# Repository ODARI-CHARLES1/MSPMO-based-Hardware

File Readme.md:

# MSPM0G350x Development Board

A hardware design for an Arduino UNO form-factor development board featuring the Texas Instruments MSPM0G350x Mixed-Signal Microcontroller with built-in CAN-FD interface.

---

## Overview

This project contains the KiCad design files for a custom development board based on the Texas Instruments MSPM0G3507 MCU, featuring CAN-FD connectivity in a familiar Arduino UNO-compatible form factor.

---
## Features

### Microcontroller

- **MCU**: Texas Instruments MSPM0G3507 (or MSPM0G3506)
- **Core**: ARM Cortex-M0+ 32-bit processor
- **Clock Speed**: Up to 80 MHz
- **Flash Memory**: 128 KB (MSPM0G3507) / 64 KB (MSPM0G3506)
- **SRAM**: 32 KB

### Integrated Peripherals

- **CAN-FD Controller**: Built-in CAN-FD with up to 5 Mbps
- **ADC**: 12-bit Analog-to-Digital Converter (up to 20 channels)
- **DAC**: 12-bit Digital-to-Analog Converter (2 channels)
- **Timers**: Multiple 16-bit and 32-bit timers
- **PWM**: High-resolution PWM outputs
- **Communication**: UART, SPI, I2C, DMA

### Board Features

- **Form Factor**: Arduino UNO R3 compatible (2.54mm pitch, 3.3V logic)
- **Power Supply**: 7-12V DC barrel jack or USB-C (5V)
- **USB Interface**: Integrated USB-C for programming and debug
- **CAN Connector**: Standard DB9 or 4-pin header for CAN-FD
- **Power LED**: Power indicator
- **User LED**: Programmable status LED on GPIO pin

---

## Pinout

### Arduino-Compatible Headers

#### Power Pins

| Pin  | Function    | Description                |
| ---- | ----------- | -------------------------- |
| VIN  | Power Input | External power (7-12V)     |
| 5V   | 5V Output   | Regulated 5V (max 500mA)   |
| 3.3V | 3.3V Output | Regulated 3.3V (max 300mA) |
| GND  | Ground      | Common ground              |
| GND  | Ground      | Common ground              |
| AREF | Analog Ref  | Analog reference voltage   |
| SDA  | I2C Data    | I2C data line (PA10)       |
| SCL  | I2C Clock   | I2C clock line (PA11)      |

#### Digital I/O Pins (Right Header)

| Pin | Arduino | MSPM0 Pin | Function                  |
| --- | ------- | --------- | ------------------------- |
| D0  | RX0     | PA8       | UART0 RX / GPIO           |
| D1  | TX0     | PA9       | UART0 TX / GPIO           |
| D2  | INT0    | PA7       | External Interrupt / GPIO |
| D3  | PWM     | PA6       | PWM / GPIO                |
| D4  | -       | PA5       | GPIO                      |
| D5  | PWM     | PA4       | PWM / GPIO                |
| D6  | PWM     | PA3       | PWM / GPIO                |
| D7  | -       | PA2       | GPIO                      |

#### Digital I/O Pins (Left Header)

| Pin | Arduino  | MSPM0 Pin | Function        |
| --- | -------- | --------- | --------------- |
| D8  | -        | PC5       | GPIO            |
| D9  | PWM      | PC4       | PWM / GPIO      |
| D10 | SPI SS   | PC3       | SPI CS / GPIO   |
| D11 | SPI MOSI | PC2       | SPI MOSI / GPIO |
| D12 | SPI MISO | PC1       | SPI MISO / GPIO |
| D13 | SPI SCK  | PC0       | SPI SCK / GPIO  |

#### Analog Pins (Bottom Header)

| Pin | Arduino  | MSPM0 Pin | Function      |
| --- | -------- | --------- | ------------- |
| A0  | ADC0     | PA26      | ADC Channel 0 |
| A1  | ADC1     | PA27      | ADC Channel 1 |
| A2  | ADC2     | PA28      | ADC Channel 2 |
| A3  | ADC3     | PA25      | ADC Channel 3 |
| A4  | ADC4/SDA | PA10      | ADC / I2C SDA |
| A5  | ADC5/SCL | PA11      | ADC / I2C SCL |

### CAN-FD Interface

| Pin   | Function | Notes                      |
| ----- | -------- | -------------------------- |
| CAN_H | CAN High | Requires 120Ω termination |
| CAN_L | CAN Low  | Requires 120Ω termination |
| GND   | Ground   | Signal ground              |

---

## Electrical Specifications

| Parameter              | Value                        |
| ---------------------- | ---------------------------- |
| Operating Voltage      | 3.3V (logic), 5V (USB power) |
| Input Voltage (Barrel) | 7-12V DC                     |
| Max Current (3.3V)     | 300 mA                       |
| Max Current (5V USB)   | 500 mA                       |
| I/O Voltage            | 3.3V (5V tolerant inputs)    |
| CAN-FD Speed           | Up to 5 Mbps                 |
| Operating Temp         | -40°C to 85°C              |

---

## Mechanical Specifications

| Parameter        | Value                              |
| ---------------- | ---------------------------------- |
| Board Dimensions | 68.6mm × 53.3mm (UNO form factor) |
| Mounting Holes   | 4× M3 holes (2.9mm diameter)      |
| Header Pitch     | 2.54mm (0.1")                      |
| PCB Thickness    | 1.6mm                              |

---

## Getting Started

### Prerequisites

- Texas Instruments MSPM0 MCU SDK
- CMSIS-DAP or compatible debug probe
- Arduino IDE with MSPM0 support

### Programming

1. **Via Debugger**: Connect a CMSIS-DAP probe to the SWD pins (SWDIO, SWDCLK, GND)
2. **Via USB**: Use the built-in USB bootloader (if programmed)

### Software Setup

```bash
# Install MSPM0 SDK
git clone https://github.com/TexasInstruments/mspm0_sdk.git

# Install ARM GCC toolchain
# Download from: https://developer.arm.com/tools-and-software/open-source-software/developer-tools/gnu-toolchain/gnu-rm
```

---

## Development Tools

- **EDA**: KiCad 8.0+
- **MCU SDK**: TI MSPM0 SDK
- **IDE**: TI Code Composer Studio or VS Code with MSPM0 plugins
- **Programmer**: CMSIS-DAP compatible probe

---

## Project Structure

```
MSPMO-based-Hardware/
├── MSPMO-based-Hardware.kicad_pro    # KiCad project file
├── MSPMO-based-Hardware.kicad_sch    # Schematic
├── MSPMO-based-Hardware.kicad_pcb    # PCB layout
├── MSPMO-based-Hardware.kicad_prl    # Layout settings
├── MSPMO-based-Hardware.kicad_dru    # Design rules
└── Readme.md                         # This file
```

---

## Hardware Design

### Power Supply Circuit

- USB-C connector for 5V input
- Barrel jack for 7-12V DC input
- AMS1117-3.3 LDO for 3.3V regulation
- LM1117-5.0 LDO for 5V regulation (optional)

### CAN-FD Transceiver

- SN65HVD230 or MCP2562 CAN-FD transceiver
- 120Ω terminating resistor (selectable)
- ESD protection on CAN lines

### Additional Components

- Reset button
- Boot selector (for bootloader)
- Power LED (green)
- User LED (red, on PC7)
- Crystal oscillator (32.768 kHz for RTC)

---

## Programming Examples

### Basic Blink

```c
#include "ti_mspm0g3507.h"

int main(void) {
    // Configure PC7 as output (User LED)
    GPIOC->DIR_b.PIN7 = GPIO_DIR_OUT;
  
    while(1) {
        GPIOC->DOUT_BSET = (1 << 7);  // LED on
        delay_ms(500);
        GPIOC->DOUT_BCLR = (1 << 7);  // LED off
        delay_ms(500);
    }
}
```

### CAN-FD Transmit

```c
#include "ti_mspm0g3507.h"
#include "can.h"

int main(void) {
    CAN_Init(CAN_BAUD_500K);
  
    CAN_TxHeaderTypeDef txHeader;
    txHeader.Id = 0x123;
    txHeader.DLC = 8;
    txHeader.IDE = CAN_ID_STD;
    txHeader.FDF = CAN_FD_CAN;
  
    uint8_t data[8] = {0x01, 0x02, 0x03, 0x04, 0x05, 0x06, 0x07, 0x08};
  
    while(1) {
        CAN_SendMessage(&txHeader, data);
        delay_ms(1000);
    }
}
```

---

## License

This hardware design is provided as-is for educational and development purposes.

---

## References

- [TI MSPM0G3507 Datasheet](https://www.ti.com/lit/ds/symlink/mspm0g3507.pdf)
- [TI MSPM0 SDK Documentation](https://dev.ti.com/tirex/explore/node?node=AGJ7H6JRK1A-jhO1mH3k0pw__LATEST)
- [CAN-FD Specification](https://www.can-cia.org/can-fd/)
- [Arduino UNO R3 Reference Design](https://store.arduino.cc/arduino-uno-rev3)

---

## Support

For issues or questions:

- Open an issue on the project repository
- Check TI's E2E forums for MSPM0-specific questions

---

**Version**: 1.0
**Date**: February 2026
**Author**: Odari-Designs

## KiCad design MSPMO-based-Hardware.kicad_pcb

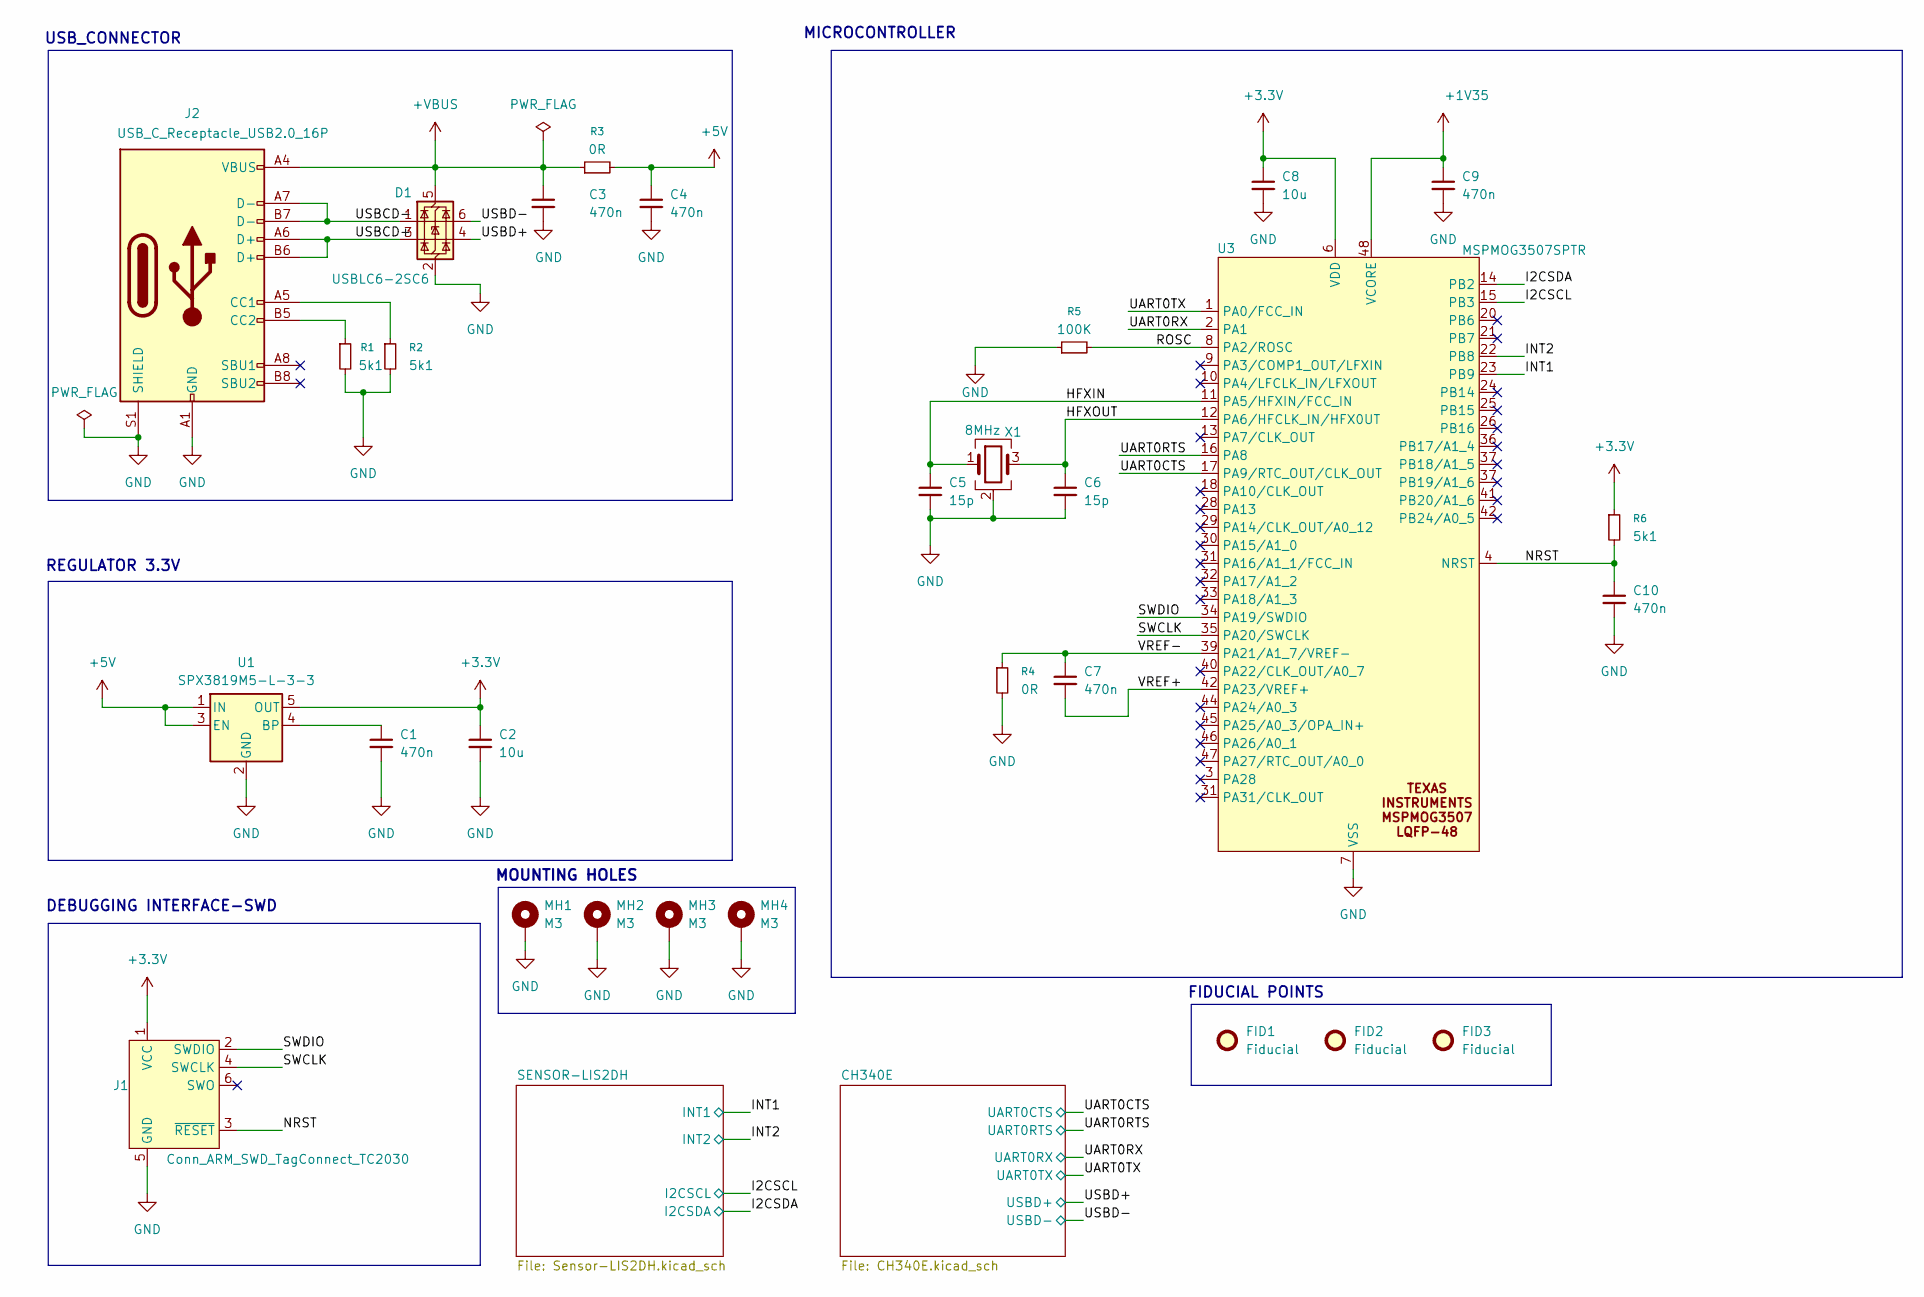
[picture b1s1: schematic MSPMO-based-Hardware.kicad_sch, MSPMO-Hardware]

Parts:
C1, C3, C4, C7, C9, C10: 470n; C_0805_2012Metric; Manufacturer part Number C0805T474K8RBLTU; LCSC C20859689
C2, C8: 10u; C_0805_2012Metric; Manufacturer part Number C0805C106K8PAC7210; LCSC C1882894
C5, C6: 15p; C_0805_2012Metric; Manufacturer part Number C0805T474K8RBLTU
D1: USBLC6-2SC6; SOT-23-6; Manufacturer part Number USBLC6-2SC6Y; LCSC C2969755
FID1, FID2, FID3: Fiducial; Fiducial_1mm_Mask2mm
J1: Conn_ARM_SWD_TagConnect_TC2030; Tag-Connect_TC2030-IDC-FP_2x03_P1.27mm_Vertical
J2: USB_C_Receptacle_USB2.0_16P; USB_C_Receptacle_GCT_USB4105-xx-A_16P_TopMnt_Horizontal; Manufacturer part Number GSB1C4621DS1HR; LCSC C20657289
MH1, MH2, MH3, MH4: M3; MountingHole_2.7mm_M2.5_Pad_Via
R1, R2, R6: 5k1; R_0603_1608Metric; Manufacturer Part Number TNPW06035K10BEEA; LCSC C2088892
R3, R4: 0R; R_0603_1608Metric; Manufacturer Part Number MCT06030C4702FP500; LCSC C1884633
R5: 100K; R_0603_1608Metric; Manufacturer Part Number TNPW0603100KFEEA; LCSC C2131840
U1: SPX3819M5-L-3-3; SOT-23-5; Manufacturer part Number SPX3819M5-L-3-3/TR
U3: MSPMOG3507SPTR; LQFP-48-1EP_7x7mm_P0.5mm_EP3.6x3.6mm_ThermalVias; Manufacturer Part Number MSPMOG3507SPTR; LCSC C22362630
X1: 8MHz; Crystal_SMD_3225-4Pin_3.2x2.5mm; Manufacturer part Number KC3225Z8.00000C1KX00; LCSC C1988275

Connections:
+1V35: C9.1, U3.48 (VCORE)
+3.3V: C2.1, C8.1, J1.1 (VCC), R6.1, U1.5 (OUT), U3.6 (VDD); also elsewhere on the board
+5V: C4.1, R3.2, U1.1 (IN), U1.3 (EN)
+VBUS: C3.1, D1.5 (VBUS), J2.A4 (VBUS), J2.A9 (VBUS), J2.B4 (VBUS), J2.B9 (VBUS), R3.1
/HFXIN: C5.1, U3.11 (PA5/HFXIN/FCC_IN), X1.1
/HFXOUT: C6.1, U3.12 (PA6/HFCLK_IN/HFX0UT), X1.3
/I2CSCL: U3.15 (PB3); also elsewhere on the board
/I2CSDA: U3.14 (PB2); also elsewhere on the board
/INT1: U3.23 (PB9); also elsewhere on the board
/INT2: U3.22 (PB8)
/NRST: C10.1, J1.3 (~RESET), R6.2, U3.4 (NRST)
/ROSC: R5.2, U3.8 (PA2/ROSC)
/SWCLK: J1.4 (SWCLK), U3.35 (PA20/SWCLK)
/SWDIO: J1.2 (SWDIO), U3.34 (PA19/SWDIO)
/UART0CTS: U3.17 (PA9/RTC_OUT/CLK_OUT); also elsewhere on the board
/UART0RTS: U3.16 (PA8); also elsewhere on the board
/UART0RX: U3.2 (PA1); also elsewhere on the board
/UART0TX: U3.1 (PA0/FCC_IN); also elsewhere on the board
/USBCD+: D1.3 (I/O2), J2.A6 (D+), J2.B6 (D+)
/USBCD-: D1.1 (I/O1), J2.A7 (D-), J2.B7 (D-)
/USBD+: D1.4 (I/O2); also elsewhere on the board
/USBD-: D1.6 (I/O1); also elsewhere on the board
/VREF+: C7.2, U3.42 (PA23/VREF+)
/VREF-: C7.1, R4.1, U3.39 (PA21/A1_7/VREF-)
GND: C1.2, C2.2, C3.2, C4.2, C5.2, C6.2, C8.2, C9.2, C10.2, D1.2 (GND), J1.5 (GND), J2.A1 (GND), J2.A12 (GND), J2.B1 (GND), J2.B12 (GND), J2.S1 (SHIELD), MH1.1, MH2.1, MH3.1, MH4.1, R1.2, R2.2, R4.2, R5.1, U1.2 (GND), U3.7 (VSS), X1.2 (G), X1.4 (G); also elsewhere on the board
unnamed: J2.A5 (CC1), R2.1
unnamed: J2.B5 (CC2), R1.1
unnamed: C1.1, U1.4 (BP)

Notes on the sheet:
DEBUGGING INTERFACE-SWD
USB_CONNECTOR
REGULATOR 3.3V
FIDUCIAL POINTS
MICROCONTROLLER
MOUNTING HOLES

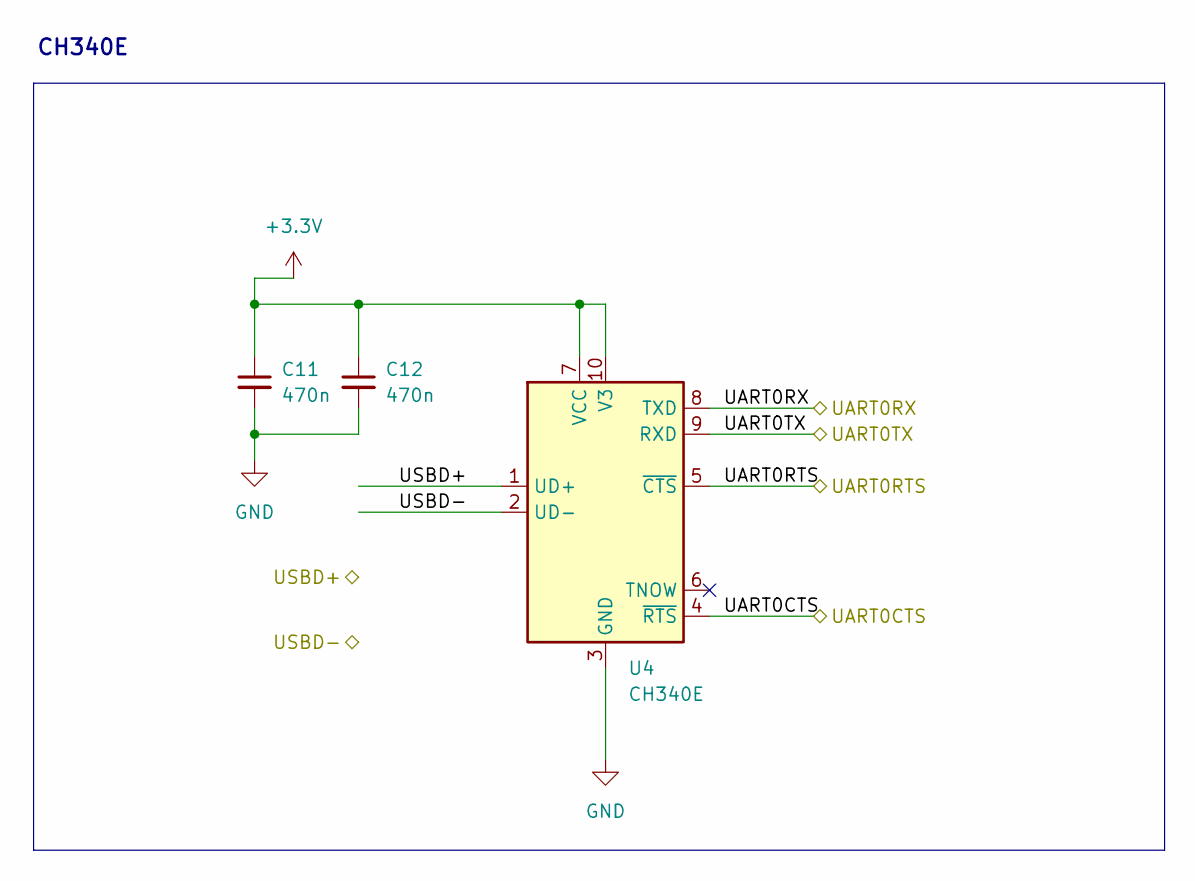
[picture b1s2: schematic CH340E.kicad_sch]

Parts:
C11, C12: 470n; C_0805_2012Metric; Manufacturer part Number C0805T474K8RBLTU; LCSC C20859689
U4: CH340E; MSOP-10_3x3mm_P0.5mm; Manufacturer part Number 5893; LCSC C99652

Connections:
+3.3V: C11.1, C12.1, U4.7 (VCC), U4.10 (V3); also elsewhere on the board
/UART0CTS: U4.4 (~RTS); also elsewhere on the board
/UART0RTS: U4.5 (~CTS); also elsewhere on the board
/UART0RX: U4.8 (TXD); also elsewhere on the board
/UART0TX: U4.9 (RXD); also elsewhere on the board
/USBD+: U4.1 (UD+); also elsewhere on the board
/USBD-: U4.2 (UD-); also elsewhere on the board
GND: C11.2, C12.2, U4.3 (GND); also elsewhere on the board

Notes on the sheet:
CH340E

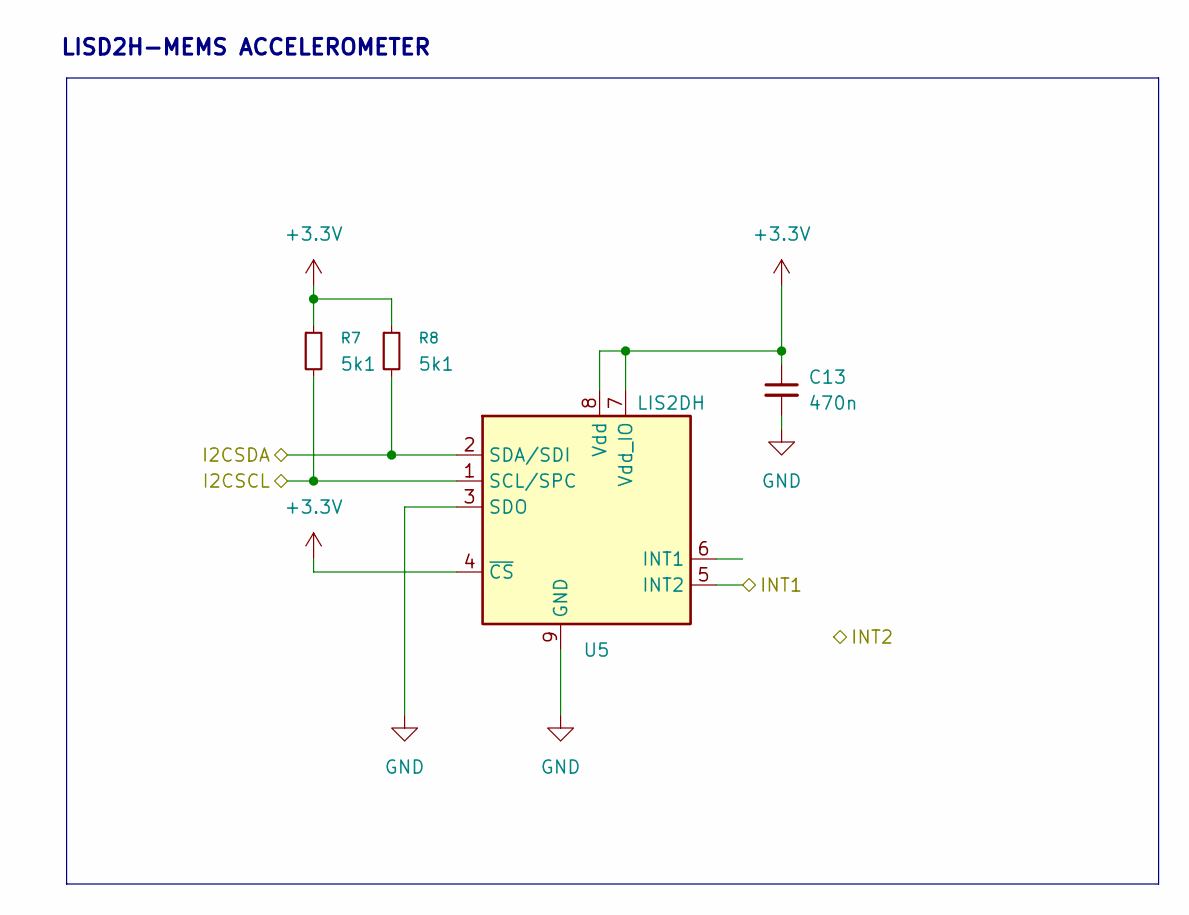
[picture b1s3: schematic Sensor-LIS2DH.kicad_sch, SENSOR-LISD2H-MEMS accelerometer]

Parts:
C13: 470n; C_0805_2012Metric; Manufacturer part Number C0805T474K8RBLTU; LCSC C20859689
R7, R8: 5k1; R_0603_1608Metric; Manufacturer Part Number TNPW06035K10BEEA; LCSC C2088892
U5: LIS2DH; LGA-14_2x2mm_P0.35mm_LayoutBorder3x4y; Manufacturer part Number LIS2DH12TR; LCSC C110926

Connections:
+3.3V: C13.1, R7.1, R8.1, U5.4 (~CS), U5.7 (Vdd_IO), U5.8 (Vdd); also elsewhere on the board
/I2CSCL: R7.2, U5.1 (SCL/SPC); also elsewhere on the board
/I2CSDA: R8.2, U5.2 (SDA/SDI); also elsewhere on the board
/INT1: U5.5 (INT2); also elsewhere on the board
GND: C13.2, U5.3 (SDO), U5.9 (GND), U5.10 (GND), U5.11 (GND), U5.12 (GND), U5.13 (GND), U5.14 (GND); also elsewhere on the board

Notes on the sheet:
LISD2H-MEMS ACCELEROMETER

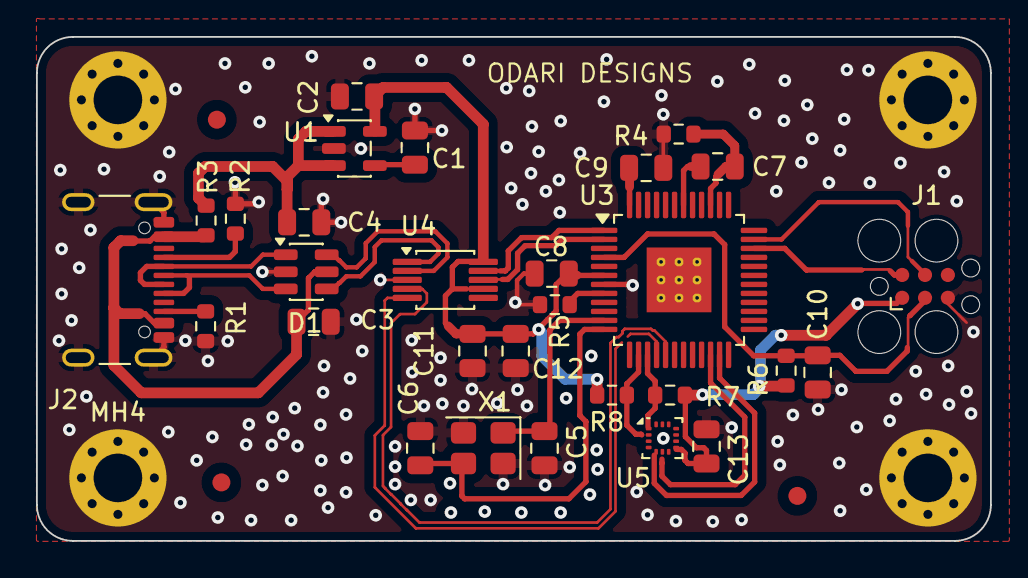
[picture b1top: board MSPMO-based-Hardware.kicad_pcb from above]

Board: 2 copper layers, 53.0 x 28.0 mm, 36 parts (0 on the bottom side), 27 nets.

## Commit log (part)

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2026-02-16 created MSPMOG3507SPTR symbol
2026-02-22 feat(hardware): add passive components and crystal to MSPM0 schematic
2026-02-22 chore(hardware): add passive components and update BOM configuration
    Add capacitors (C1-C6), resistors (R1-R3), and crystal (X1) to the MSPM0G3507 schematic with associated power decoupling and filtering circuitry. Update BOM export path to Docs folder and add distrib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
2026-02-28 chore(config): add ESP-IDF EIM configuration file
    Add EIM configuration for ESP-IDF v5.5.3 environment setup including
    paths, tool configurations, mirrors, and Python environment settings.
2026-02-28 chore(hardware): adjust component positions in KiCad PCB layout
    Repositioned multiple passive components (resistors and capacitors) and IC to resolve silkscreen overlap and improve PCB layout density. Modified positions for C4, C9, C10, C11, C12, C13, R1, R3, R4,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
2026-02-28 docs: add main schematic PDF documentation
2026-02-28 chore(hardware): adjust C3 capacitor position in PCB layout
2026-02-28 docs: update Readme with board layout images and improved table formatting
2026-02-28 docs: add board layout PCB image to Readme
2026-02-28 docs: add PCB board images to documentation
2026-03-03 update the schematic file
2026-03-04 featardware): major(h PCB redesign with USB-C, SWD programming, and sensor integration
    Redesigned MSPM0-based hardware PCB with significant changes:
    - Added USB-C receptacle with ESD protection (USBLC6-2SC6)
    - Added Tag-Connect TC2030 SWD programming header
    - Added LIS2DH 3-axis accelerometer with I2C interface
    - Added CH340E USB-to-serial converter for UART debugging
    - Added SPX3819 LDO voltage regulator (3.3V output)
2026-03-04 chore(hardware): update KiCad project settings with enhanced design rules and net class configuration
2026-03-04 feat(hardware): add fiducial markers and mounting holes to PCB schematic
    Add manufacturing aids to the KiCad schematic including:
    - Three fiducial markers (FID1, FID2, FID3) for SMT alignment during assembly
    - Four M3 mounting holes with connected pads (MH1-MH4) for secure PCB mounting
    - Associated GND connections and text labels for documentation
    - Also adds KLC compliance properties to various schematic components
2026-03-04 fix(hardware): update LIS2DH sensor schematic with corrected routing and metadata
    - Adjust wire routing for INT1 signal path on Sensor-LIS2DH schematic
    - Update datasheet URL to STMicroelectronics lis2dh12.pdf
    - Add manufacturer, supplier, and part number metadata to component
    - Add KLC compliance properties (KLC_S3.3, KLC_S4.1) to symbol and footprint entries
2026-03-05 feat(hardware): add CH340E USB-to-Serial converter schematic
    Add CH340E USB-to-UART converter IC with associated decoupling capacitors
    and filtering components for USB connectivity. The circuit includes 470nF
    capacitors on USB lines, power conditioning, and UART signal connections.
2026-03-05 feat(hardware): add net class configurations for I2C, UART, USB and new component sheets
    Add net class presets and pattern assignments for I2C, UART, and USB protocols in KiCad project. Include new sheets for CH340E USB-to-Serial converter and LIS2DH sensor. Relax ERC checks for pin driv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
2026-03-05 feat(hardware): add net class configurations and relax ERC settings
    Configure net class patterns for USB, UART, and I2C protocols with designated colors and wire widths. Add CH340E and SENSOR-LIS2DH sheets to the design hierarchy. Relax ERC constraints by changing pi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
2026-03-05 feat(hardware): add CH340E USB-to-serial and LIS2DH sensor sub-sheets with I2C/UART connectivity
    - Add CH340E USB-to-serial converter sheet with UART0 and USB signals
    - Add LIS2DH accelerometer sensor sheet with I2C and interrupt pins
    - Add PWR_FLAG symbols for improved ERC compliance
    - Rename DEBUGGING INTERFACE to DEBUGGING INTERFACE-SWD
    - Rename USB_C to USB_CONNECTOR for clarity
    - Reorganize component placement and routing
2026-03-05 feat(hardware): add SWD interface, I2C sensor, and USB-UART to schematic
    - Added PWR_FLAG symbols for power indication
    - Renamed DEBUGGING INTERFACE to DEBUGGING INTERFACE-SWD
    - Renamed USB_C to USB_CONNECTOR
    - Added CH340E USB-to-Serial converter sheet with UART signals
    - Added LIS2DH accelerometer sensor sheet with I2C and interrupt signals
    - Relocated components and rerouted wires for improved layout
2026-03-06 Update:add TC2030 for debugging interface
2026-03-10 feat(hardware): add KLC compliance properties and supplier metadata to schematic components
    Adds KiCad Library Convention properties (KLC_S3.3, KLC_S4.1) to multiple components for compliance, and includes manufacturer, part number, and distributor links (Mouser, DigiKey, LCSC) to the CH340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
2026-03-10 feat(hardware): add custom design rules for JLCPCB manufacturing
    Add MSPMO-based-Hardware.kicad_dru with DRC rules matching JLCPCB
    capabilities including track width, clearance, hole size, and
    silkscreen requirements for outer and inner layers.
2026-03-15 chore(config): add .kinotes to gitignore
2026-03-15 chore(hardware): reposition components and add design to PCB layout
2026-03-15 docs: add MSPMO hardware diagram image
2026-03-22 feat(hardware): add L2 GND ground plane zone to PCB layout
    - Added new bottom copper layer GND polygon zone (L2_GND) for improved ground connectivity
    - Updated zone connection settings for GND pin to optimize electrical performance
    - These changes enhance the PCB's grounding design and signal integrity
2026-03-22 fix(hardware): update pad dimensions for PCB footprint
2026-03-23 feat(hardware): add routing vias and reposition PCB components
    Add approximately 50 new vias with copper trace segments to improve PCB routing connectivity. Reposition multiple components including capacitors (C2-C13), resistors (R1-R5, R8), and IC (U1) to optim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
2026-03-23 fix(hardware): update PCB routing clearance and track width constraints
    - Reduce clearance from 0.2mm to 0.152mm for the 12-bit bus class
    - Add 0.3mm and 0.4mm track width options while removing 0.75mm
    - These changes optimize PCB routing rules for the bus width configuration
2026-03-30 fix(hardware): rearrange hierarchical labels in CH340E schematic
    Swapped positions of USBD-/USBD+ with UART0RTS/UART0CTS signal labels and adjusted their orientation and placement coordinates in the KiCad schematic.
2026-03-30 fix(hardware): remap USB differential signals to UART flow control pins
    Renamed hierarchical labels in CH340E schematic to properly map USB D+/D- signals to UART0 RTS/CTS pins, correcting the signal routing configuration.
2026-03-30 fix(hardware): update PCB design rules and track width constraints
    Updates KiCad design rules by reducing minimum clearance from 0.152mm to 0.1mm, adding new track widths (0.05, 0.1, 0.15, 0.25mm), and adjusting differential pair width from 0.2mm to 0.25mm to improv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
2026-03-30 fix(hardware): reposition USB CDC differential signal labels in schematic
2026-03-30 fix(hardware): rearrange LIS2DH schematic hierarchical labels
2026-04-01 fix(hardware): reposition components and optimize PCB routing
    - Relocated J1 Tag-Connect header and J2 USB-C connector to resolve routing conflicts
    - Adjusted resistor and capacitor positions (R2, R3, R6, R8, C3, C6, C7, C9, C10, C13)
    - Realigned U5 LIS2DH12 accelerometer for better placement
    - Added new vias and net segments to improve signal routing
    - Expanded GND copper pours on both F.Cu and B.Cu layers
2026-04-01 fix(hardware): update BOM export path to parent directory
2026-04-01 fix(hardware): reposition INT2 hierarchical label in LIS2DH schematic
2026-04-02 Chore: update the pcb layout
2026-06-01 chore(config): specify step file name in project settings
2026-06-01 build(hardware): add STEP model for mechanical integration
    Include the MSPMO-based-Hardware.step file to enable 3D CAD workflows and mechanical assembly verification.
2026-06-01 feat(hardware): add STL mesh for 3D printing
    Add the MSPMO-based-Hardware.stl file to support rapid prototyping and 3D printing workflows.
2026-06-01 build(enclosure): add STEP model for mechanical design
    Include the MSPMO-based-Hardware.step file to facilitate CAD integration and enclosure design workflows.
2026-06-01 feat(enclosure): add assembly STL mesh
    Add the STL mesh file for the enclosure assembly to support 3D printing workflows.
